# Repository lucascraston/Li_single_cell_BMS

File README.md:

# Li_single_cell_BMS

 -This is a Battery Management System (BMS) for a single cell Li-ion or Li-Po battery. I am currently on version 1 of this design, the PCB has been ordered along with the parts and I will assemble and test it when everything arrives.

-I will be adding a BOM for this build, along with a breakdown of the price per component and the total cost to manufactur each board.

-I will also be performing thorough tests on the board to verify its functionilty and I will record the results to upload them. To accompany the tests, I am aiming to complete a Worst Case Circuit Analysis (WCCA) of my design BEFORE I assemble and test. This will help me with determining the expected operating region for each part to ensure I meet my requirments, and to ensure I am within the manufacturers limits.

**A relatively minor mistake was made on the schematic side, which translated into a larger mistake on the PCB.... I will post the updated schematic, maybe you can spot the difference? Anyways, the error would make the charge over current part of the circuit usless, which is was already because the limit is set to over 2.5A, and my charge IC can only do 0.5A. Either way, it is still a mistake, so I am going to fix it in the CAD software and either order another set of PCBs, or mod the ones I already ordered....TBD.**
# Tests to perform:
- [ ] Verify discharge overcurrent and short circuit functionality (Based off N-channel MOSFETs Rds-ON)
- [ ] Test P-channel MOSFET load switch when 5V is applied
- [ ] Verify charge current (Based off resistor choice)
- [ ] verify UVP & OVP charge parameters of charger IC (Based off individual IC)
- [ ] Test charge overcurrent value (The battery should never reach this charge current based on IC choice, use lab PSU)
- [ ] Verify  OVP & UVP parameters of protection IC (Based off individual IC)
# Version 1 Features:
- 0-500 mA charging rate
- Over voltage charge protection: OVP = 4.28V 
- Under voltage discharge protection: UVP = 2.8V 
- Over current discharge protection: OCD = 0.09V (Vss to V-)
- Over current charge protection: OCC = -0.09V (Vss to V-)
- Short circuit protection: SCD = 0.3V
- Load disconnects when charging
- Charging and fully charged LED status indicator
- USB mini B receptacle for charging

# Improvements to be made:
- [ ] 5V boost and 3.3V LDO output rails
- [ ] Go from 2 layer to 4 layer board
- [ ] Onboard battery percentage / status indicator. Maybe this is not neccessary if we are interfacing with a MCU?
- [ ] 5M gate to source pull down resistors
- [ ] 5V input pad to charge battery without USB
- [ ] Dual MOSFET array package to reduce size and cost
- [ ] 1W current sense resistor to make the current limit easier to adjust and test

# Build and Testing

The boards arrived and I have built two so far. I have tested them and everything seems to be working. I am hoping to create a document that outlines each test case and records the testing data to share it on here. I would like to create an automated test script for my scope but It would be difficult without a programmabled PSU...one day.

# To be completed
- [ ] WCCA 
- [ ] Testing documentation

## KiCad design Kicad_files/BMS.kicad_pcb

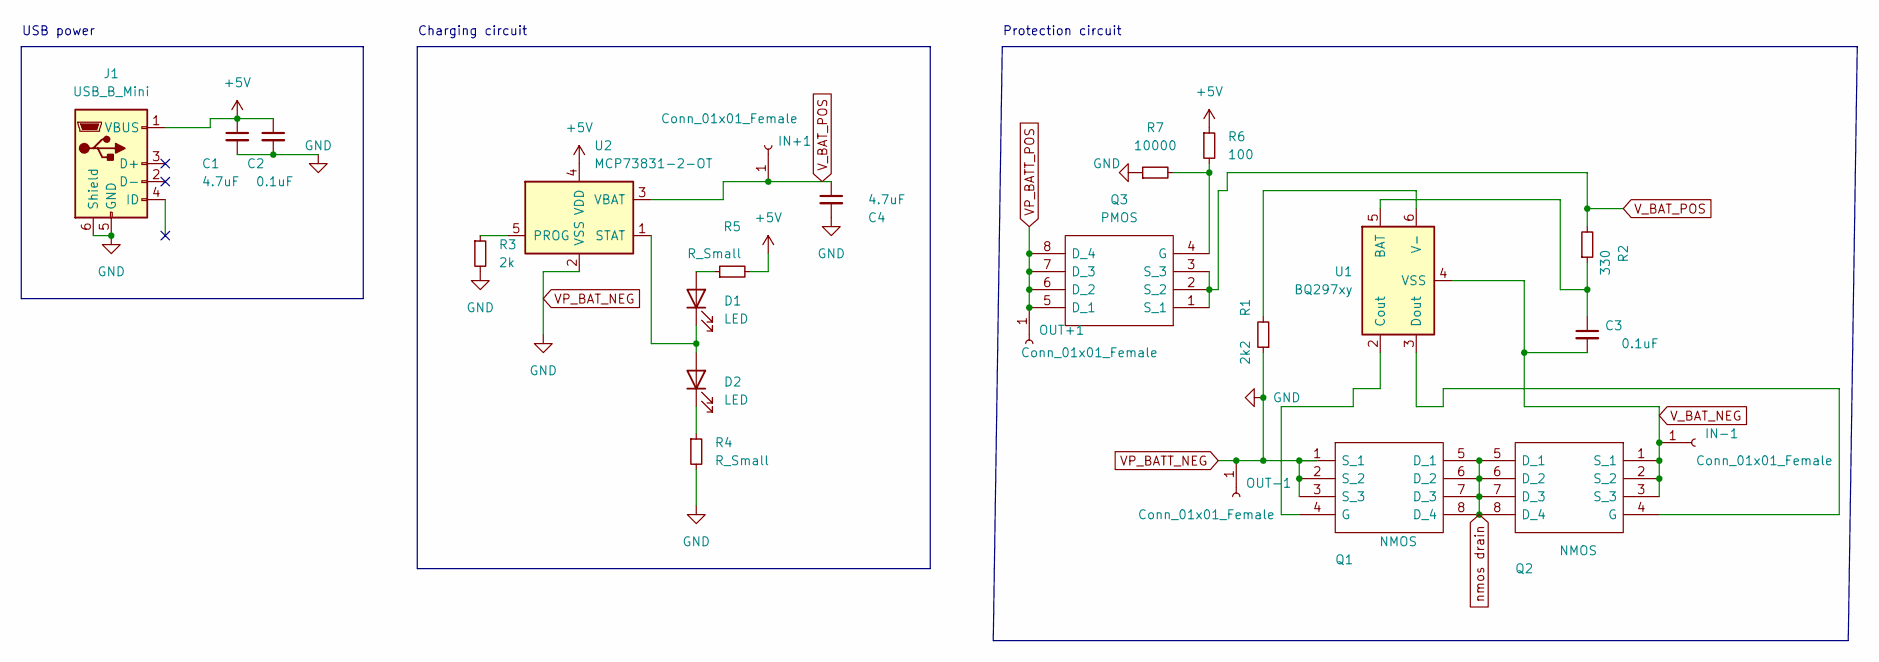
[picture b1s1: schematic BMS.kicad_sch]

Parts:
C1, C4: 4.7uF; C_0805_2012Metric_Pad1.18x1.45mm_HandSolder
C2, C3: 0.1uF; C_0805_2012Metric_Pad1.18x1.45mm_HandSolder
D1, D2: LED; LED_0603_1608Metric_Pad1.05x0.95mm_HandSolder
IN+1: Conn_01x01_Female; TestPoint_Pad_3.0x3.0mm
IN-1: Conn_01x01_Female; TestPoint_Pad_3.0x3.0mm
J1: USB_B_Mini; USB_Mini-B_Lumberg_2486_01_Horizontal
OUT+1: Conn_01x01_Female; TestPoint_Pad_3.0x3.0mm
OUT-1: Conn_01x01_Female; TestPoint_Pad_3.0x3.0mm
Q1, Q2: NMOS; SQJ418EPT1_GE3; Manufacturer_Part_Number SQJ418EP-T1_GE3; Mouser Part Number 78-SQJ418EP-T1_GE3
Q3: PMOS; SQJ418EPT1_GE3; Manufacturer_Part_Number SQJ418EP-T1_GE3; Mouser Part Number 78-SQJ418EP-T1_GE3
R1: 2k2; R_0805_2012Metric_Pad1.20x1.40mm_HandSolder
R2: 330; R_0805_2012Metric_Pad1.20x1.40mm_HandSolder
R3: 2k; R_0805_2012Metric_Pad1.20x1.40mm_HandSolder
R4, R5: R_Small; R_0805_2012Metric_Pad1.20x1.40mm_HandSolder
R6: 100; R_0805_2012Metric_Pad1.20x1.40mm_HandSolder
R7: 10000; R_0805_2012Metric_Pad1.20x1.40mm_HandSolder
U1: BQ297xy; WSON-6_1.5x1.5mm_P0.5mm
U2: MCP73831-2-OT; SOT-23-5

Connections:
+5V: C1.1, C2.1, J1.1 (VBUS), R5.2, R6.1, U2.4 (VDD)
unnamed: C3.1, R2.1, U1.5 (BAT)
unnamed: D1.1 (K), D2.2 (A), U2.1 (STAT)
unnamed: D1.2 (A), R5.1
unnamed: D2.1 (K), R4.1
unnamed: Q1.4 (G), U1.2 (Cout)
unnamed: Q2.4 (G), U1.3 (Dout)
unnamed: Q3.4 (G), R6.2, R7.2
unnamed: R1.2, U1.6 (V-)
unnamed: R3.1, U2.5 (PROG)
VP_BATT_NEG: C1.2, C2.2, C4.2, J1.5 (GND), J1.6 (Shield), OUT-1.1, Q1.1 (S_1), Q1.2 (S_2), Q1.3 (S_3), R1.1, R3.2, R4.2, R7.1, U2.2 (VSS)
VP_BATT_POS: OUT+1.1, Q3.5 (D_1), Q3.6 (D_2), Q3.7 (D_3), Q3.8 (D_4)
V_BAT_NEG: C3.2, IN-1.1, Q2.1 (S_1), Q2.2 (S_2), Q2.3 (S_3), U1.4 (VSS)
V_BAT_POS: C4.1, IN+1.1, Q3.1 (S_1), Q3.2 (S_2), Q3.3 (S_3), R2.2, U2.3 (VBAT)
nmos drain: Q1.5 (D_1), Q1.6 (D_2), Q1.7 (D_3), Q1.8 (D_4), Q2.5 (D_1), Q2.6 (D_2), Q2.7 (D_3), Q2.8 (D_4)

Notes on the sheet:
USB power
Charging circuit
Protection circuit

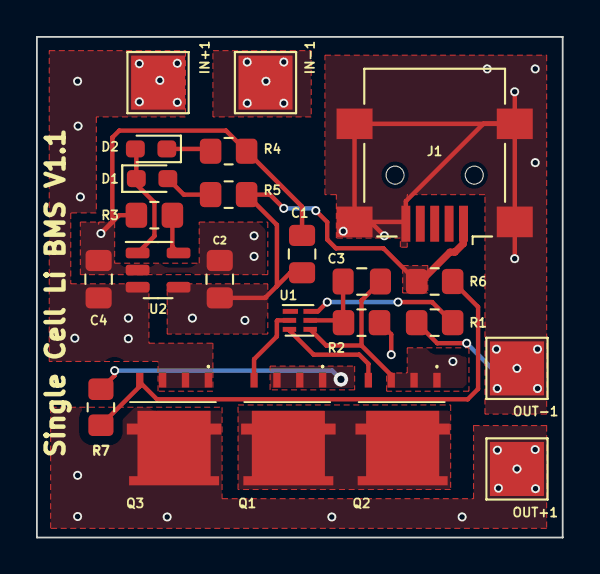
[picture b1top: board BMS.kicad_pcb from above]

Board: 2 copper layers, 29.2 x 27.8 mm, 23 parts (0 on the bottom side), 15 nets.

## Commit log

2022-11-02 added screenshots of pcb,scheme, and 3d view
2022-11-03 added more readme info
2022-11-03 updated schematic image
2022-11-03 updated readme info and added photo to readme
2022-11-03 Updated readme documentation
2022-11-03 renamed image files for specefic version andreadme
2022-11-03 updated image file names and readme for context
2022-11-03 added updated schematic image
2022-11-03 new 3D image
2022-11-03 new 3D render screen shot
2022-11-06 updated kicad images
2022-11-06 new kicad files to reflect v1.1 changes
2022-11-06 new gerbers for new v1.1 board
2022-11-06 changed readme content
2022-11-07 added new readme comments
2022-11-07 Added bom part list and cost
2022-11-21 readme update
2022-11-21 feature description update
2022-11-25 added bew readme info and images
2022-11-30 updated image to show build
2022-11-30 adjusted image size
2022-11-30 changed image size
2022-12-04 added better quality image to readme
2022-12-04 re-cropped the image in readme
2022-12-04 foldered some items
2023-12-08 added bill of materials to readme
